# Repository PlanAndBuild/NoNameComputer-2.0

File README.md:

<div align="center">
  
</div>

---

<h1 align="center">NNCpro</h1>

<h3 align="center">AKA NoNameComputer 2.0</h3>

<p align="center">
 <small><I>Built for sky.<I></small>
</p>

<p align="center">
  <b>NNCpro is a fligth computer designed mainly for rockets but it also can be used for other vehicles.</b>
  <br>
  <b>It is designed to collect data from all of the sensor, sending it IRL back down to the earth via radio link, deploy parachutes, steer rocket in flight using aerodynamic control or TVC and at the end send live location. </b>
  </br>
  <em>We have designed it for our rockets because there is no comercial computers or if there is something it's very expensive. We actually like designig electronics and thats why we're even here.</em>
</p>

## Features

**8x Servo outputs** ***(PWM channels)***

**6x Pyrotechniacal channels** ***(used for firing parachute charges, motor ignitions etc.)***

**Long-Range radio** ***(based on two LoRa modules for simultaneous transmiting and reciveing)***

**Current and Voltage sensing** ***(based on INA3221 three channel current sensor)***

**Audio signaling** ***(using passive buzzer with possibility of modulation sound wave)***

**Flash memory for storing software and flight data in flight**

**micro-SD card slot for saving fligth data after landing**

**3,3v and 5v power supply**

**ARGB LEDs for signaling computer states**

---
## Sensors
| Sensor Type | Primary Component |
| :--- | :--- |
| **Barometer main** | `MS5611` (High precision) |
| **Barometer secondary** |`BMP390` (Redundant) |
| **Inertail Mesurment Unit main**| `LSM6DSV80XTR` (6-DoF Main) |
| **Inertail Mesurment Unit secondary** |`LSM6DSO32XTR` (6-DoF Secondary) |
| **High-G Acceleration** | `H3LIS200DLTR` (Up to $\pm200\text{g}$) |
| **Magnetometer** | `MMC5983MA` (3-axis Compass) |
| **GNSS (GPS)** | `u-blox MAX-M10M-20b` |
---
## Images

<table align="center" border="0" cellpadding="0" cellspacing="0">
  <tr>
    <td>
      
    </td>
    <td>
      
    </td>
  </tr>
</table>

### schematics:

 <div align="center">

</div>
 
## ⚖️ License

This project is licensed under the **Creative Commons Attribution-NonCommercial-ShareAlike 4.0 International (CC BY-NC-SA 4.0)** License.

[![CC BY-NC-SA 4.0][cc-by-nc-sa-shield]][cc-by-nc-sa]

You are free to share and adapt this material under the following terms:
* **Attribution** — You must give appropriate credit to the original author.
* **NonCommercial** — You may not use the material for commercial purposes.
* **ShareAlike** — If you remix, transform, or build upon the material, you must distribute your contributions under the same license.

## BOM
| Item No. | Qty | Value | Manufacturer Part Number (MPN) | Supplier Part Number | Unit Price | Total Price |
| :---: | :---: | :--- | :--- | :--- | :---: | :---: |
|   | **--- CAPACITORS ---** |   |   |   |   |   |
| 1 | 1 | 10nF | 0603X7R103K250NT | [C49326603](https://www.lcsc.com/product-detail/C49326603.html) | $0.0034 | $0.0034 |
| 2 | 33 | 100nF | FCC0603B104K500CT | [C5137636](https://www.lcsc.com/product-detail/C5137636.html) | $0.0147 | $0.4851 |
| 3 | 5 | 1uF | CL10B105KA8NNNC | [C29936](https://www.lcsc.com/product-detail/C29936.html) | $0.0218 | $0.1090 |
| 4 | 2 | 2.2uF | CL10A225KO8NNNC | [C23630](https://www.lcsc.com/product-detail/C23630.html) | $0.0093 | $0.0186 |
| 5 | 1 | 4.7uF | CL10A475KO8NNNC | [C19666](https://www.lcsc.com/product-detail/C19666.html) | $0.0227 | $0.0227 |
| 6 | 5 | 10uF | CL10A106MA8NRNC | [C96446](https://www.lcsc.com/product-detail/C96446.html) | $0.0532 | $0.2660 |
| 7 | 5 | 22uF | CL10A226MP8NUNE | [C86295](https://www.lcsc.com/product-detail/C86295.html) | $0.0380 | $0.1900 |
| 8 | 4 | 47uF | CL21A476MRYNNNE | [C377776](https://www.lcsc.com/product-detail/C377776.html) | $0.0542 | $0.2168 |
|   | **--- RESISTORS ---** |   |   |   |   |   |
| 9 | 3 | 0.03Ω | YLRY06-1-30F | [C20608713](https://www.lcsc.com/product-detail/C20608713.html) | $0.0390 | $0.1170 |
| 10 | 13 | 10Ω | 1RC0603J0100 | [C54531635](https://www.lcsc.com/product-detail/C54531635.html) | $0.0012 | $0.0156 |
| 11 | 7 | 220Ω | HRC0603F2200ENTN | [C54920883](https://www.lcsc.com/product-detail/C54920883.html) | $0.0011 | $0.0077 |
| 12 | 1 | 560Ω | GR0603J560RT5G00 | [C49653272](https://www.lcsc.com/product-detail/C49653272.html) | $0.0008 | $0.0008 |
| 13 | 1 | 1kΩ | FRC0603F1001TS | [C2907002](https://www.lcsc.com/product-detail/C2907002.html) | $0.0023 | $0.0023 |
| 14 | 2 | 4.7kΩ | HRC0603J472 ENTN | [C54921051](https://www.lcsc.com/product-detail/C54921051.html) | $0.0010 | $0.0020 |
| 15 | 2 | 5.1kΩ | RTT035101FTP | [C103686](https://www.lcsc.com/product-detail/C103686.html) | $0.0012 | $0.0024 |
| 16 | 30 | 10kΩ | FRC0603F1002TS | [C2906982](https://www.lcsc.com/product-detail/C2906982.html) | $0.0023 | $0.0690 |
| 17 | 2 | 15kΩ | SCR0603J15K | [C3017711](https://www.lcsc.com/product-detail/C3017711.html) | $0.0009 | $0.0018 |
| 18 | 1 | 30kΩ | CL0603JN30KP | [C49254202](https://www.lcsc.com/product-detail/C49254202.html) | $0.0011 | $0.0110 |
| 19 | 1 | 42.2kΩ | RS-03K4222FT | [C321903](https://www.lcsc.com/product-detail/C321903.html) | $0.0006 | $0.0006 |
| 20 | 10 | 100kΩ | CL0603JN100KP | [C46635231](https://www.lcsc.com/product-detail/C46635231.html) | $0.0011 | $0.0110 |
| 21 | 1 | 110kΩ | CL0603FN110KP | [C48996812](https://www.lcsc.com/product-detail/C48996812.html) | $0.0012 | $0.0012 |
| 22 | 1 | 135kΩ | RT0603BRD07135KL | [C861113](https://www.lcsc.com/product-detail/C861113.html) | $0.0284 | $0.0284 |
| 23 | 1 | 330kΩ | GR0603J330KT5G00 | [C49656714](https://www.lcsc.com/product-detail/C49656714.html) | $0.0008 | $0.0008 |
|   | **--- INDUCTORS / CHOKES ---** |   |   |   |   |   |
| 24 | 2 | 27nH | LQG15HS27NJ02D | [C12669](https://www.lcsc.com/product-detail/C12669.html) | $0.0282 | $0.0564 |
| 25 | 1 | 680nH | 7443934450068 | [710-7443934450068](https://www.mouser.pl/ProductDetail/Wurth-Elektronik/7443934450068) | $1.8700 | $1.8700 |
| 26 | 1 | 1.5uH | AFE201612S1R5MBT | [C41347749](https://www.lcsc.com/product-detail/C41347749.html) | $0.0389 | $0.0389 |
|   | **--- DIODES / TRANSISTORS ---** |   |   |   |   |   |
| 27 | 6 | ZMM3V0-TD | ZMM3V0-TD | [C46550821](https://www.lcsc.com/product-detail/C46550821.html) | $0.0064 | $0.0384 |
| 28 | 7 | DO2300B | DO2300B | [C41367404](https://www.lcsc.com/product-detail/C41367404.html) | $0.0190 | $0.1330 |
| 29 | 12 | LED RED | GL0805UR01 | [C51933307](https://www.lcsc.com/product-detail/C51933307.html) | $0.0046 | $0.0552 |
| 30 | 1 | SI1016CX-T1-GE3 | SI1016CX-T1-GE3 | [C727293](https://www.lcsc.com/product-detail/C727293.html) | $0.9442 | $0.9442 |
| 31 | 3 | SP15100L | SP15100L | [C20199370](https://www.lcsc.com/product-detail/C20199370.html) | $0.1170 | $0.3510 |
| 32 | 3 | WS2812B-2020 | XL-0807RGBC-2812B-S | [C41413181](https://www.lcsc.com/product-detail/C41413181.html) | $0.0345 | $0.1035 |
|   | **--- INTEGRATED CIRCUITS (ICs) ---** |   |   |   |   |   |
| 33 | 2 | 74LVC2G04LT06ARCQ | 74LVC2G04LT06ARCQ | [C46527078](https://www.lcsc.com/product-detail/C46527078.html) | $0.0404 | $0.0808 |
| 34 | 1 | BMP390L | BMP390L | [828-BMP390TR-ND](https://www.digikey.pl/en/products/detail/bosch-sensortec/BMP390/16164575) | $3.3000 | $3.3000 |
| 35 | 2 | E220-400M22S | E220-400M22S | [C2971737](https://www.lcsc.com/product-detail/C2971737.html) | $2.7215 | $5.4430 |
| 36 | 1 | H3LIS200DLTR | H3LIS200DLTR | [497-15698-2-ND](https://www.digikey.pl/en/products/detail/stmicroelectronics/H3LIS200DLTR/5268010) | $8.4000 | $8.4000 |
| 37 | 1 | INA3221 | INA3221AIRGVR | [C181255](https://www.lcsc.com/product-detail/C181255.html) | $1.4247 | $1.4247 |
| 38 | 1 | LSM6DSO32 | LSM6DSO32 | [497-LSM6DSO32XTR-ND](https://www.digikey.pl/en/products/detail/stmicroelectronics/LSM6DSO32XTR/14291421) | $4.8900 | $4.8900 |
| 39 | 1 | LSM6DSV80XTR | LSM6DSV80XTR | [497-LSM6DSV80XTR-ND](https://www.digikey.pl/en/products/detail/stmicroelectronics/LSM6DSV80XTR/26371340) | $6.5100 | $6.5100 |
| 40 | 1 | LT6000CDCB#TRMPBF | LT6000CDCB#TRMPBF | [C672644](https://www.lcsc.com/product-detail/C672644.html) | $3.3445 | $3.3445 |
| 41 | 1 | MAX-M10M-20B | MAX-M10M-20B | [672-MAX-M10M-20BTR-ND](https://www.digikey.pl/en/products/detail/u-blox/MAX-M10M-20B/28314774) | $7.5600 | $7.5600 |
| 42 | 1 | MMC5983MA | MMC5983MA | [C404329](https://www.lcsc.com/product-detail/C404329.html) | $2.2672 | $2.2672 |
| 43 | 1 | MS5611 | MS5611-01BA | [C15639](https://www.lcsc.com/product-detail/C15639.html) | $7.1145 | $7.1145 |
| 44 | 1 | NC7WZ07P6X | NC7WZ07P6X | [C95342](https://www.lcsc.com/product-detail/C95342.html) | $0.0564 | $0.0564 |
| 45 | 1 | PCA9685BS | PCA9685BS | [C5191634](https://www.lcsc.com/product-detail/C5191634.html) | $4.4014 | $4.4014 |
| 46 | 1 | STM32H562RIVx | STM32H562RIV6 | [497-STM32H562RIV6-ND](https://www.digikey.pl/en/products/detail/stmicroelectronics/STM32H562RIV6/21348982) | $7.3400 | $7.3400 |
| 47 | 1 | TPS564242DRLR | TPS564242DRLR | [296-TPS564242DRLRTR-ND](https://www.digikey.pl/en/products/detail/texas-instruments/TPS564242DRLR/16585669) | $0.5800 | $0.5800 |
| 48 | 1 | TPS56C230RJER | TPS56C230RJER | [C1849534](https://www.lcsc.com/product-detail/C1849534.html) | $0.5300 | $0.5300 |
| 49 | 1 | W25Q512JVE | W25Q512JVEIQ | [C2986165](https://www.lcsc.com/product-detail/C2986165.html) | $6.7941 | $6.7941 |
|   | **--- CONNECTORS ---** |   |   |   |   |   |
| 50 | 2 | Conn_01x02_Pin | 2.54mm Header 2pin | [Numer](Link) | | |
| 51 | 8 | Conn_01x03_Pin | 2.54mm Header 3pin | [Numer](Link) | | |
| 52 | 2 | SMA_Connector | HL-SMA-KHDC5T | [C19712117](https://www.lcsc.com/product-detail/C19712117.html) | $2.9083 | $5.8166 |
| 53 | 1 | U.fl_Connetor | 5001-RF00001-03R1-00 | [C48689029](https://www.lcsc.com/product-detail/C48689029.html) | $0.0338 | $0.0338 |
| 54 | 1 | MLD-TF PUSH-H18 | MLD-TF PUSH-H18 | [C52750848](https://www.lcsc.com/product-detail/C52750848.html) | $0.0421 | $0.0421 |
| 55 | 7 | Screw_Terminal_01x02 | KF301-2P | [C474881](https://www.lcsc.com/product-detail/C474881.html) | $0.1008 | $0.7056 |
| 56 | 1 | USB_C_Receptacle_USB2.0_16P | F32258MUBCE2O | [C5917305](https://www.lcsc.com/product-detail/C5917305.html) | $0.3052 | $0.3052 |
|   | **--- MISCELLANEOUS ---** |   |   |   |   |   |
| 57 | 6 | 500mA | CF06V5TR50 | [C163116](https://www.lcsc.com/product-detail/C163116.html) | $0.0386 | $0.2316 |
| 58 | 3 | 600ohm | CBG160808U601T | [C73326](https://www.lcsc.com/product-detail/C73326.html) | $0.0113 | $0.0678 |
| 59 | 1 | Buzzer | YX-SMD8530P | [C781886](https://www.lcsc.com/product-detail/C781886.html) | $0.3755 | $0.3755 |
| 60 | 1 | Crystal_GND24 | F32258MUBCE2O | [C5917305](https://www.lcsc.com/product-detail/C5917305.html) | $0.3052 | $0.3052 |
|   | **--- ADDITIONAL ELEMENTS ---** |   |   |   |   |   |
| 61 | 4 | Screws | Any M3 screw |  |  |  |
| 62 | 1 | PCB Board | 4layer PCB | - | $7.0000 | $7.0000 |
|   |   |   |   |   |   |   |
| **SUMMARY** | | | | | | **Total: $90.28** |

[cc-by-nc-sa]: http://creativecommons.org/licenses/by-nc-sa/4.0/
[cc-by-nc-sa-shield]: https://img.shields.io/badge/License-CC%20BY--NC--SA%204.0-lightgrey.svg

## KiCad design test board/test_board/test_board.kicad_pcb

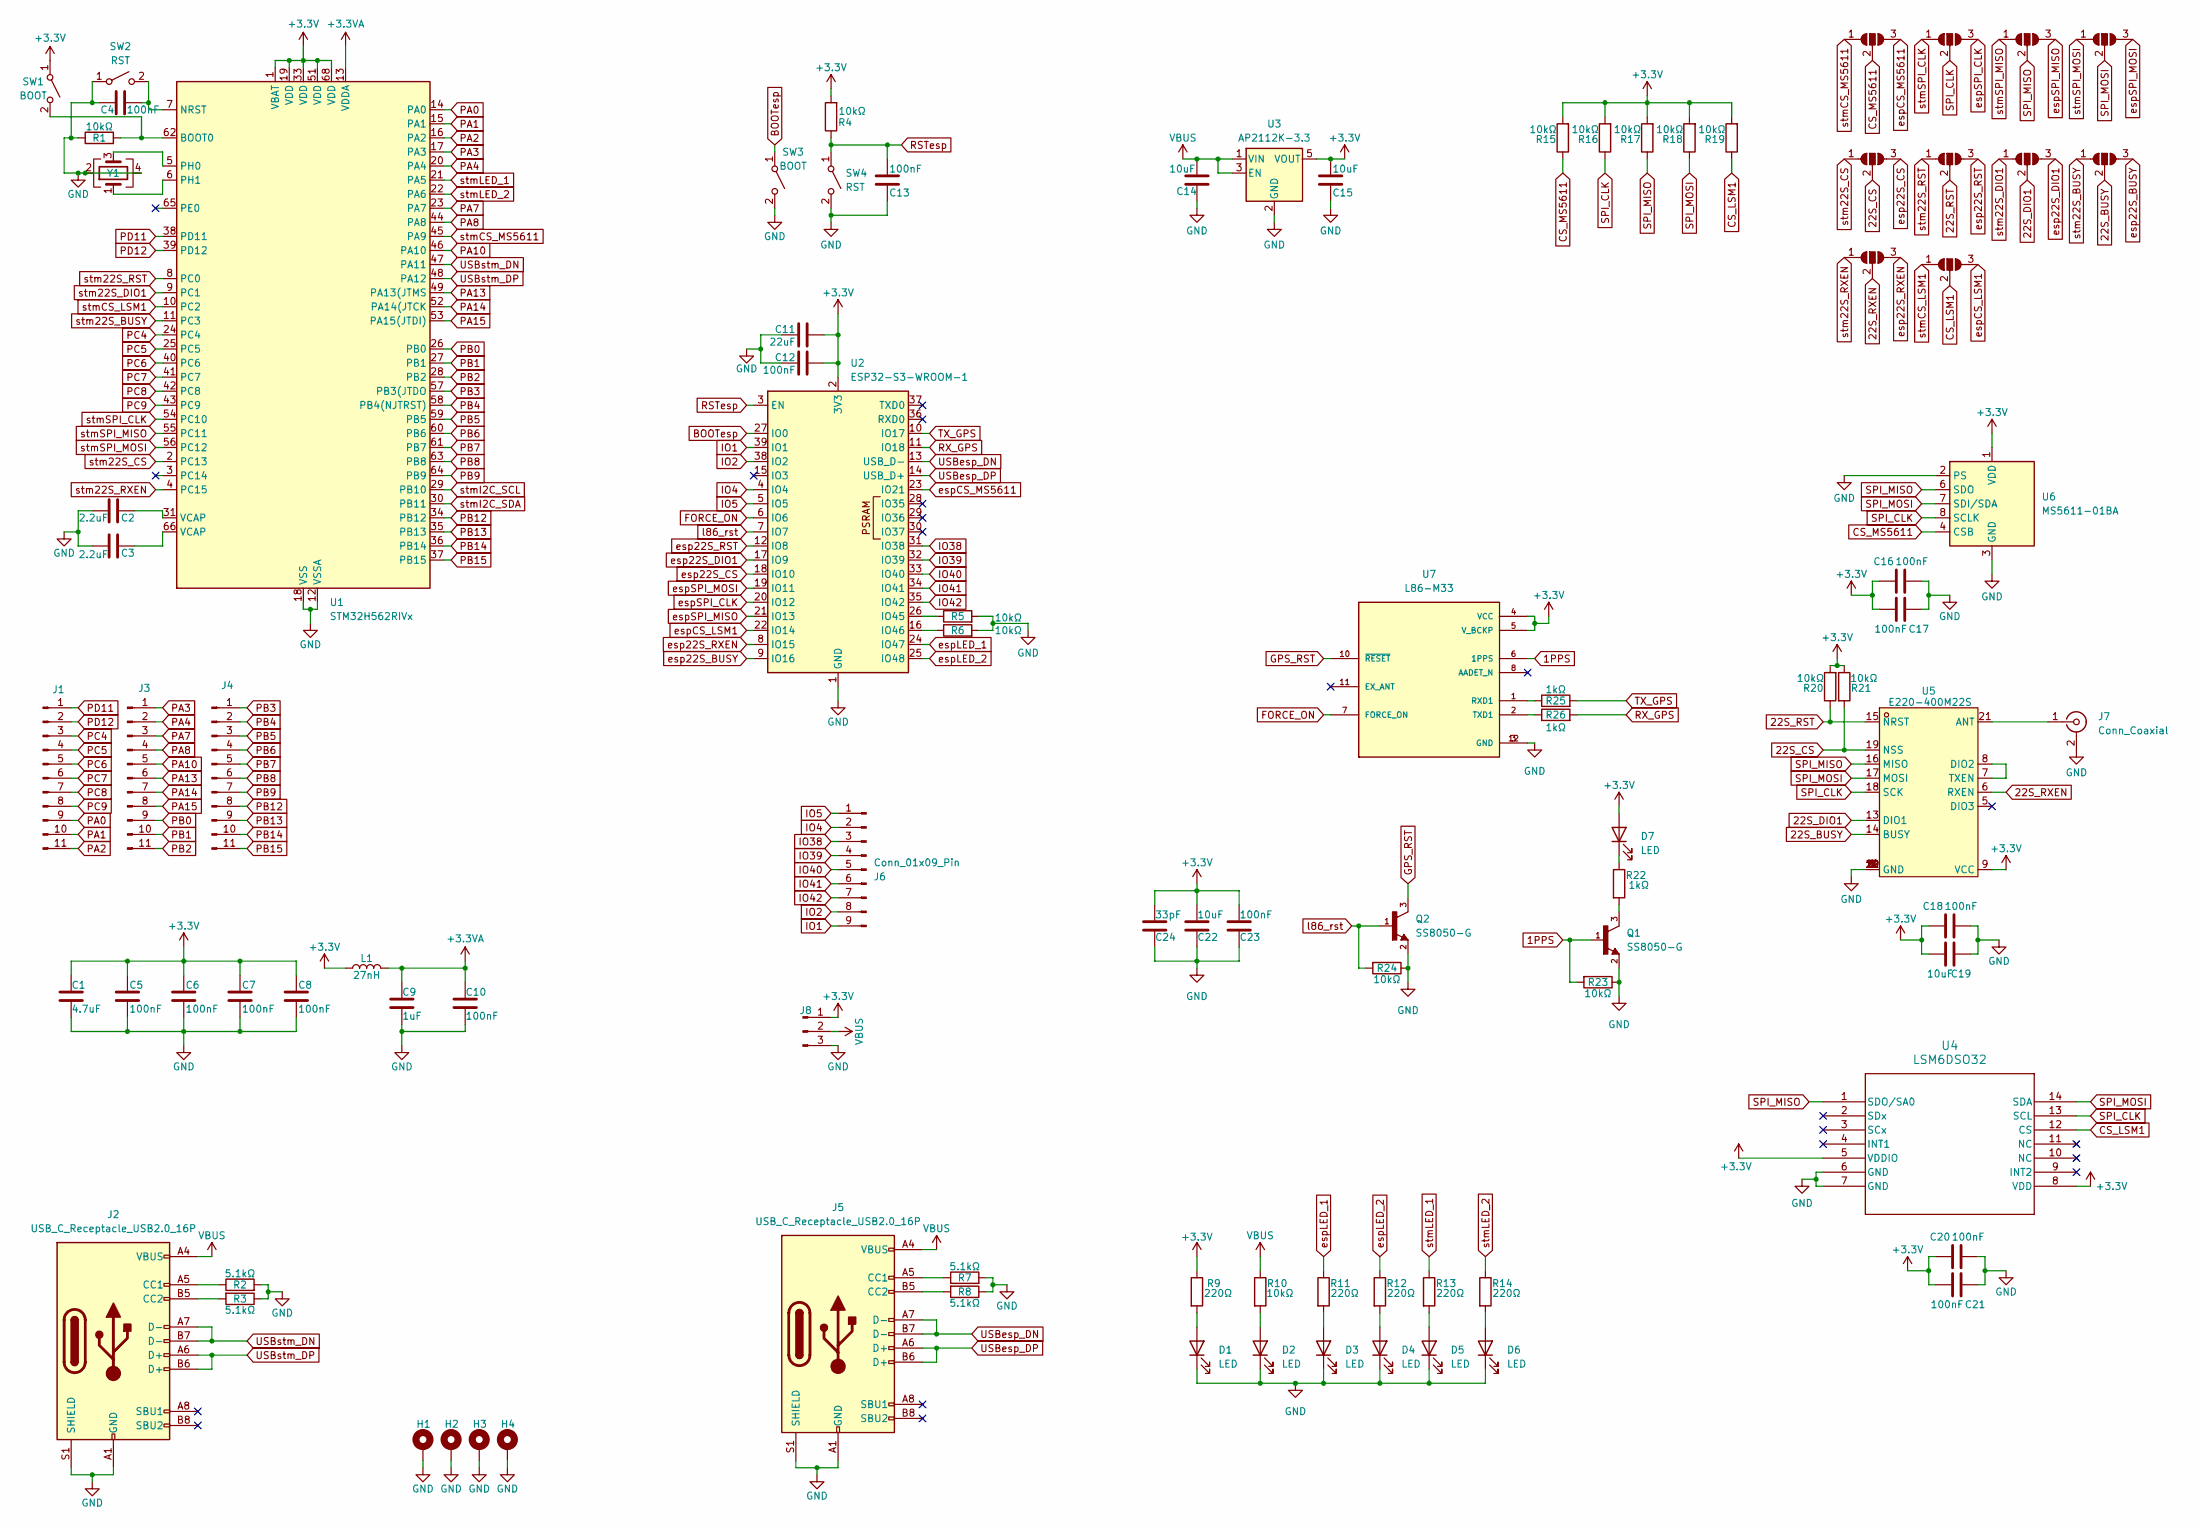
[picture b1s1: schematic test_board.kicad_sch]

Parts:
C1: 4.7uF; C_0603_1608Metric
C2, C3: 2.2uF; C_0603_1608Metric
C4, C5, C6, C7, C8, C10, C12, C13, C16, C17, C18, C20, C21, C23: 100nF; C_0603_1608Metric
C9: 1uF; C_0603_1608Metric
C11: 22uF; C_0805_2012Metric
C14, C15, C19, C22: 10uF; C_0603_1608Metric
C24: 33pF; C_0603_1608Metric
D1, D2, D3, D4, D5, D6, D7: LED; LED_0805_2012Metric
H1, H2, H3, H4: MountingHole_Pad; MountingHole_3mm_Pad_Via
J1, J3, J4: Conn_01x11_Pin; PinHeader_1x11_P2.54mm_Vertical
J2, J5: USB_C_Receptacle_USB2.0_16P; USB_C_Receptacle_GCT_USB4105-xx-A_16P_TopMnt_Horizontal
J6: Conn_01x09_Pin; PinSocket_1x09_P2.54mm_Vertical
J7: Conn_Coaxial; SMA_Molex_73251-1153_EdgeMount_Horizontal
J8: Conn_01x03_Pin; PinSocket_1x03_P2.54mm_Vertical
JP1, JP2, JP3, JP4, JP5, JP6, JP7, JP8, JP9, JP10: SolderJumper_3_Open; SolderJumper-3_P1.3mm_Open_RoundedPad1.0x1.5mm_NumberLabels
L1: 27nH; L_0603_1608Metric
Q1, Q2: SS8050-G; TRANS_SS8050-G; PARTREV A
R1, R4, R5, R6, R10, R15, R16, R17, R18, R19, R20, R21, R23, R24: 10kΩ; R_0603_1608Metric
R2, R3, R7, R8: 5.1kΩ; R_0603_1608Metric
R9, R11, R12, R13, R14: 220Ω; R_0603_1608Metric
R22, R25, R26: 1kΩ; R_0603_1608Metric
SW1, SW3: BOOT; SW_Tactile_SPST_NO_Straight_CK_PTS636Sx25SMTRLFS
SW2, SW4: RST; SW_Tactile_SPST_NO_Straight_CK_PTS636Sx25SMTRLFS
U1: STM32H562RIVx; QFN-68-1EP_8x8mm_P0.4mm_EP5.2x5.2mm; Manufacturer_Part_Number STM32H5RIV6
U2: ESP32-S3-WROOM-1; ESP32-S3-WROOM-1U
U3: AP2112K-3.3; SOT-23-5
U4: LSM6DSO32; LGA-14L_2P5X3X0P83_STM; Manufacturer_Part_Number LSM6DSO32
U5: E220-400M22S; WIRELM-SMD_22P-L20.0-W14.0-P1.27-BR; LCSC Part C2971737
U6: MS5611-01BA; LGA-8_3x5mm_P1.25mm; Manufacturer_Part_Number MS5611-01BA
U7: L86-M33; XCVR_L86-M33
Y1: Crystal_GND24; Crystal_SMD_3225-4Pin_3.2x2.5mm

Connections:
1PPS: Q1.1, R23.2, U7.6 (1PPS)
22S_BUSY: JP10.2 (C), U5.14 (BUSY)
22S_CS: JP2.2 (C), R21.2, U5.19 (NSS)
22S_DIO1: JP8.2 (C), U5.13 (DIO1)
22S_RST: JP5.2 (C), R20.1, U5.15 (NRST)
22S_RXEN: JP3.2 (C), U5.6 (RXEN)
+3.3V: C1.1, C5.1, C6.1, C7.1, C8.1, C11.2, C12.2, C15.2, C16.1, C17.2, C18.1, C19.2, C20.1, C21.2, C22.1, C23.1, C24.1, D7.2 (A), J8.1, L1.1, R4.2, R9.1, R15.2, R16.2, R17.2, R18.2, R19.2, R20.2, R21.1, SW1.1 (A), U1.1 (VBAT), U1.19 (VDD), U1.33 (VDD), U1.51 (VDD), U1.68 (VDD), U2.2 (3V3), U3.5 (VOUT), U4.5 (VDDIO), U4.8 (VDD), U5.9 (VCC), U6.1 (VDD), U7.4 (VCC), U7.5 (V_BCKP)
+3.3VA: C9.1, C10.1, L1.2, U1.13 (VDDA)
BOOTesp: SW3.1 (A), U2.27 (IO0)
CS_LSM1: JP6.2 (C), R19.1, U4.12 (CS)
CS_MS5611: JP1.2 (C), R15.1, U6.4 (CSB), U6.5 (CSB)
FORCE_ON: U2.6 (IO6), U7.7 (FORCE_ON)
GND: C1.2, C2.2, C3.2, C4.1, C5.2, C6.2, C7.2, C8.2, C9.2, C10.2, C11.1, C12.1, C13.1, C14.1, C15.1, C16.2, C17.1, C18.2, C19.1, C20.2, C21.1, C22.2, C23.2, C24.2, D1.1 (K), D2.1 (K), D3.1 (K), D4.1 (K), D5.1 (K), D6.1 (K), H1.1, H2.1, H3.1, H4.1, J2.A1 (GND), J2.A12 (GND), J2.B1 (GND), J2.B12 (GND), J2.S1 (SHIELD), J5.A1 (GND), J5.A12 (GND), J5.B1 (GND), J5.B12 (GND), J5.S1 (SHIELD), J7.2 (Ext), J8.3, Q1.2, Q2.2, R1.1, R2.2, R3.1, R5.2, R6.2, R7.2, R8.1, R23.1, R24.1, SW2.1 (A), SW3.2 (B), SW4.2 (B), U1.12 (VSSA), U1.18 (VSS), U1.32 (VSS), U1.50 (VSS), U1.67 (VSS), U1.69 (VSS), U2.1 (GND), U2.40 (GND), U2.41 (GND), U3.2 (GND), U4.6 (GND), U4.7 (GND), U5.1 (GND), U5.2 (GND), U5.3 (GND), U5.4 (GND), U5.10 (GND), U5.11 (GND), U5.12 (GND), U5.20 (GND), U5.22 (GND), U6.2 (PS), U6.3 (GND), U7.3 (GND), U7.12 (GND), Y1.2, Y1.4; also elsewhere on the board
GPS_RST: Q2.3, U7.10 (~RESET)
IO1: J6.9, U2.39 (IO1)
IO2: J6.8, U2.38 (IO2)
IO4: J6.2, U2.4 (IO4)
IO5: J6.1, U2.5 (IO5)
IO38: J6.3, U2.31 (IO38)
IO39: J6.4, U2.32 (IO39)
IO40: J6.5, U2.33 (IO40)
IO41: J6.6, U2.34 (IO41)
IO42: J6.7, U2.35 (IO42)
unnamed: C2.1, U1.31 (VCAP)
unnamed: C3.1, U1.66 (VCAP)
unnamed: D1.2 (A), R9.2
unnamed: D2.2 (A), R10.2
unnamed: D3.2 (A), R11.2
unnamed: D4.2 (A), R12.2
unnamed: D5.2 (A), R13.2
unnamed: D6.2 (A), R14.2
unnamed: D7.1 (K), R22.1
unnamed: J2.A5 (CC1), R2.1
unnamed: J2.B5 (CC2), R3.2
unnamed: J5.A5 (CC1), R7.1
unnamed: J5.B5 (CC2), R8.2
unnamed: J7.1 (In), U5.21 (ANT)
unnamed: Q1.3, R22.2
unnamed: R1.2, SW1.2 (B), U1.62 (BOOT0)
unnamed: C4.2, SW2.2 (B), U1.7 (NRST)
unnamed: U1.5 (PH0), Y1.3
unnamed: U1.6 (PH1), Y1.1
unnamed: R5.1, U2.26 (IO45)
unnamed: R6.1, U2.16 (IO46)
unnamed: U5.7 (TXEN), U5.8 (DIO2)
unnamed: R25.1, U7.1 (RXD1)
unnamed: R26.1, U7.2 (TXD1)
PA0: J1.9, U1.14 (PA0)
PA1: J1.10, U1.15 (PA1)
PA2: J1.11, U1.16 (PA2)
PA3: J3.1, U1.17 (PA3)
PA4: J3.2, U1.20 (PA4)
PA7: J3.3, U1.23 (PA7)
PA8: J3.4, U1.44 (PA8)
PA10: J3.5, U1.46 (PA10)
PA13: J3.6, U1.49 (PA13(JTMS)
PA14: J3.7, U1.52 (PA14(JTCK)
PA15: J3.8, U1.53 (PA15(JTDI))
PB0: J3.9, U1.26 (PB0)
PB1: J3.10, U1.27 (PB1)
PB2: J3.11, U1.28 (PB2)
PB3: J4.1, U1.57 (PB3(JTDO)
PB4: J4.2, U1.58 (PB4(NJTRST))
PB5: J4.3, U1.59 (PB5)
PB6: J4.4, U1.60 (PB6)
PB7: J4.5, U1.61 (PB7)
PB8: J4.6, U1.63 (PB8)
PB9: J4.7, U1.64 (PB9)
PB12: J4.8, U1.34 (PB12)
PB13: J4.9, U1.35 (PB13)
PB14: J4.10, U1.36 (PB14)
PB15: J4.11, U1.37 (PB15)
PC4: J1.3, U1.24 (PC4)
PC5: J1.4, U1.25 (PC5)
PC6: J1.5, U1.40 (PC6)
PC7: J1.6, U1.41 (PC7)
PC8: J1.7, U1.42 (PC8)
PC9: J1.8, U1.43 (PC9)
PD11: J1.1, U1.38 (PD11)
PD12: J1.2, U1.39 (PD12)
RSTesp: C13.2, R4.1, SW4.1 (A), U2.3 (EN)
RX_GPS: R26.2, U2.11 (IO18)
SPI_CLK: JP4.2 (C), R16.1, U4.13 (SCL), U5.18 (SCK), U6.8 (SCLK)
SPI_MISO: JP7.2 (C), R17.1, U4.1 (SDO/SA0), U5.16 (MISO), U6.6 (SDO)
SPI_MOSI: JP9.2 (C), R18.1, U4.14 (SDA), U5.17 (MOSI), U6.7 (SDI/SDA)
TX_GPS: R25.2, U2.10 (IO17); also elsewhere on the board
USBesp_DN: J5.A7 (D-), J5.B7 (D-), U2.13 (USB_D-)
USBesp_DP: J5.A6 (D+), J5.B6 (D+), U2.14 (USB_D+)
USBstm_DN: J2.A7 (D-), J2.B7 (D-), U1.47 (PA11)
USBstm_DP: J2.A6 (D+), J2.B6 (D+), U1.48 (PA12)
VBUS: C14.2, J2.A4 (VBUS), J2.A9 (VBUS), J2.B4 (VBUS), J2.B9 (VBUS), J5.A4 (VBUS), J5.A9 (VBUS), J5.B4 (VBUS), J5.B9 (VBUS), J8.2, R10.1, U3.1 (VIN), U3.3 (EN)
esp22S_BUSY: JP10.3 (B), U2.9 (IO16)
esp22S_CS: JP2.3 (B), U2.18 (IO10)
esp22S_DIO1: JP8.3 (B), U2.17 (IO9)
esp22S_RST: JP5.3 (B), U2.12 (IO8)
esp22S_RXEN: JP3.3 (B), U2.8 (IO15)
espCS_LSM1: JP6.3 (B), U2.22 (IO14)
espCS_MS5611: JP1.3 (B), U2.23 (IO21)
espLED_1: R11.1, U2.24 (IO47)
espLED_2: R12.1, U2.25 (IO48)
espSPI_CLK: JP4.3 (B), U2.20 (IO12)
espSPI_MISO: JP7.3 (B), U2.21 (IO13)
espSPI_MOSI: JP9.3 (B), U2.19 (IO11)
l86_rst: Q2.1, R24.2, U2.7 (IO7)
stm22S_BUSY: JP10.1 (A), U1.11 (PC3)
stm22S_CS: JP2.1 (A), U1.2 (PC13)
stm22S_DIO1: JP8.1 (A), U1.9 (PC1)
stm22S_RST: JP5.1 (A), U1.8 (PC0)
stm22S_RXEN: JP3.1 (A), U1.4 (PC15)
stmCS_LSM1: JP6.1 (A), U1.10 (PC2)
stmCS_MS5611: JP1.1 (A), U1.45 (PA9)
stmI2C_SCL: U1.29 (PB10)
stmI2C_SDA: U1.30 (PB11)
stmLED_1: R13.1, U1.21 (PA5)
stmLED_2: R14.1, U1.22 (PA6)
stmSPI_CLK: JP4.1 (A), U1.54 (PC10)
stmSPI_MISO: JP7.1 (A), U1.55 (PC11)
stmSPI_MOSI: JP9.1 (A), U1.56 (PC12)

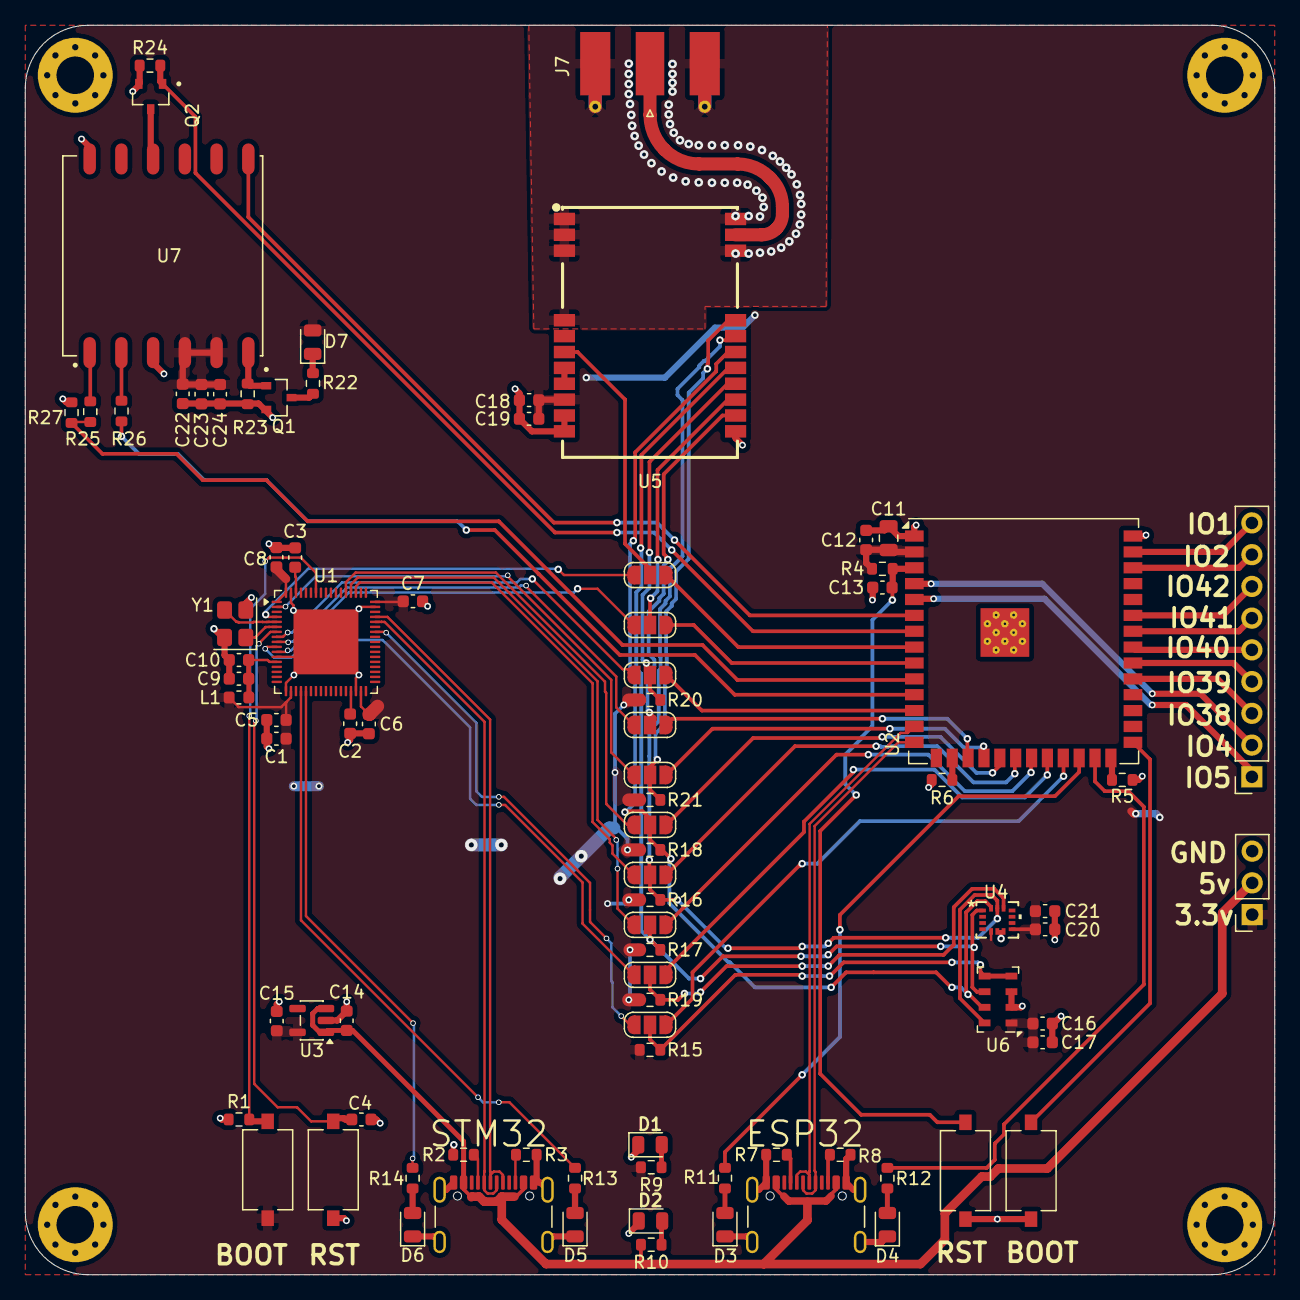
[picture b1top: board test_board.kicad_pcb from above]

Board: 2 copper layers, 100.0 x 100.0 mm, 92 parts (0 on the bottom side), 83 nets.

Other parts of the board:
R27: 5.6kΩ; R_0603_1608Metric

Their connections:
GND: R27.2; also elsewhere on the board
TX_GPS: R27.1; also elsewhere on the board

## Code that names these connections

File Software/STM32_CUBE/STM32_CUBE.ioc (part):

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Mcu.Name=STM32H562RIVx
Mcu.Package=VFQFPN68
Mcu.UserName=STM32H562RIVx
PA0.Mode=Asynchronous
PA0.Signal=UART4_TX
PA1.GPIOParameters=GPIO_Label
PA1.GPIO_Label=GPS_RST
PA1.Signal=GPIO_Output
PA10.GPIOParameters=GPIO_Label
PA10.GPIO_Label=CS_MAG
PA10.Signal=GPIO_Output
PA11.Mode=Device
PA11.Signal=USB_DM
PA12.Mode=Device
PA12.Signal=USB_DP
PA13(JTMS/SWDIO).GPIOParameters=GPIO_Label
PA13(JTMS/SWDIO).GPIO_Label=CS_H3L
PA13(JTMS/SWDIO).Signal=GPIO_Output
PA14(JTCK/SWCLK).GPIOParameters=GPIO_Label
PA14(JTCK/SWCLK).GPIO_Label=CS_LSM1
PA14(JTCK/SWCLK).Signal=GPIO_Output
PA15(JTDI).GPIOParameters=GPIO_Label
PA15(JTDI).GPIO_Label=BUSY_2
PA15(JTDI).Signal=GPIO_Input
PA3.Mode=quad_mode
PA3.Signal=OCTOSPI1_CLK
PA4.GPIOParameters=GPIO_Label
PA4.GPIO_Label=EN_5V
PA4.Signal=GPIO_Output
PA5.GPIOParameters=GPIO_Label
PA5.GPIO_Label=LED_1
PA5.Signal=GPIO_Output
PA6.Mode=OCTOSPI1_IO[3\:0]
PA6.Signal=OCTOSPI1_IO3
PA7.GPIOParameters=GPIO_Label
PA7.GPIO_Label=PYRO_1
PA7.Signal=GPIO_Output
PA9.GPIOParameters=GPIO_Label
PA9.GPIO_Label=CS_MS5611
PA9.Signal=GPIO_Output
PB0.Mode=OCTOSPI1_IO[3\:0]
PB0.Signal=OCTOSPI1_IO1
PB1.GPIOParameters=GPIO_Label
PB1.GPIO_Label=P_DET_2
PB1.Signal=GPIO_Input
PB10.Mode=I2C
PB10.Signal=I2C2_SCL
PB11.Mode=I2C
PB11.Signal=I2C2_SDA
PB12.GPIOParameters=GPIO_Label
PB12.GPIO_Label=P_DET_3
PB12.Signal=GPIO_Input
PB13.GPIOParameters=GPIO_Label
PB13.GPIO_Label=P_DET_6
PB13.Signal=GPIO_Input
PB14.GPIOParameters=GPIO_Label
PB14.GPIO_Label=PYRO_6
PB14.Signal=GPIO_Output
PB15.GPIOParameters=GPIO_Label
PB15.GPIO_Label=P_DET_5
PB15.Signal=GPIO_Input
PB2.GPIOParameters=GPIO_Label
PB2.GPIO_Label=PYRO_3
PB2.Signal=GPIO_Output
PB6.Mode=quad_mode
PB6.Signal=OCTOSPI1_NCS
PB7.GPIOParameters=GPIO_Label
PB7.GPIO_Label=CS_LoRa2
PB7.Signal=GPIO_Output
PB8.Mode=Asynchronous
PB8.Signal=UART4_RX
PB9.GPIOParameters=GPIO_Label
PB9.GPIO_Label=DIO1_2
PB9.Signal=GPIO_Output
PC0.GPIOParameters=GPIO_Label
PC0.GPIO_Label=SepDet1
PC0.Signal=GPIO_Input
PC1.GPIOParameters=GPIO_Label
PC1.GPIO_Label=SepDet2
PC1.Signal=GPIO_Input
PC10.Mode=Full_Duplex_Master
PC10.Signal=SPI3_SCK
PC11.Mode=Full_Duplex_Master
PC11.Signal=SPI3_MISO
PC12.Mode=Full_Duplex_Master
PC12.Signal=SPI3_MOSI
PC13.GPIOParameters=GPIO_Label
PC13.GPIO_Label=CS_LoRa1
PC13.Signal=GPIO_Output
PC14-OSC32_IN(OSC32_IN).GPIOParameters=GPIO_Label
PC14-OSC32_IN(OSC32_IN).GPIO_Label=DIO1_1
PC14-OSC32_IN(OSC32_IN).Signal=GPIO_Output
PC15-OSC32_OUT(OSC32_OUT).GPIOParameters=GPIO_Label
PC15-OSC32_OUT(OSC32_OUT).GPIO_Label=CS_BMP390
PC15-OSC32_OUT(OSC32_OUT).Signal=GPIO_Output
PC2.Mode=OCTOSPI1_IO[3\:0]
PC2.Signal=OCTOSPI1_IO2
PC3.Mode=OCTOSPI1_IO[3\:0]
PC3.Signal=OCTOSPI1_IO0
PC4.GPIOParameters=GPIO_Label
PC4.GPIO_Label=P_DET_1
PC4.Signal=GPIO_Input
PC5.GPIOParameters=GPIO_Label
PC5.GPIO_Label=PYRO_2
PC5.Signal=GPIO_Output
PC6.GPIOParameters=GPIO_Label
PC6.GPIO_Label=PYRO_4
PC6.Signal=GPIO_Output
PC7.GPIOParameters=GPIO_Label
PC7.GPIO_Label=CS_SD
PC7.Signal=GPIO_Output
PC8.GPIOParameters=GPIO_Label
PC8.GPIO_Label=CS_LSM2
PC8.Signal=GPIO_Output
PD11.GPIOParameters=GPIO_Label
PD11.GPIO_Label=PYRO_5
PD11.Signal=GPIO_Output
PD12.GPIOParameters=GPIO_Label
PD12.GPIO_Label=P_DET_4
PD12.Signal=GPIO_Input
PE0.GPIOParameters=GPIO_Label
PE0.GPIO_Label=BUSY_1
PE0.Signal=GPIO_Input
PH0-OSC_IN(PH0).Mode=HSE-External-Oscillator
PH0-OSC_IN(PH0).Signal=RCC_OSC_IN
PH1-OSC_OUT(PH1).Mode=HSE-External-Oscillator
PH1-OSC_OUT(PH1).Signal=RCC_OSC_OUT
RCC.HSE_VALUE=8000000
RCC.SYSCLKFreq_VALUE=240000000
RCC.SYSCLKSource=RCC_SYSCLKSOURCE_PLLCLK
board=custom

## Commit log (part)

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2026-06-17 first
2026-06-19 added Zine
2026-06-20 Updated PCB, repo structure, readme
2026-06-21 added software
2026-06-21 bom added
2026-06-21 addet gitignore
2026-06-21 gitignore
2026-06-21 Fix: zastosowanie .gitignore i usuniecie smieci
2026-06-21 gitignore update
2026-06-24 BOM update
2026-06-24 update bom
2026-06-24 Convert BOM.csv to a standard CSV format
2026-06-24 Update BOM.csv header format
2026-06-24 Add BOM section with component details to README
    Added a Bill of Materials (BOM) section to the README with detailed component listings, including capacitors, resistors, inductors, diodes, integrated circuits, connectors, and miscellaneous items.
2026-06-24 price update
2026-06-24 Add schematics section with images to README
    Added schematic images section to README.
2026-06-24 added schematic photos
2026-06-24 Fix heading format for schematics section
